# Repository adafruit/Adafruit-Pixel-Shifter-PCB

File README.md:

## Adafruit Pixel Shifter - For Addressable LEDs PCB

<a href="http://www.adafruit.com/products/6066"><br/>
Click here to purchase one from the Adafruit shop</a>

PCB files for the Adafruit Pixel Shifter - For Addressable LEDs. 

Format is EagleCAD schematic and board layout
* https://www.adafruit.com/product/6066

### Description

We've been stocking WS2811-n-friends for a long time, enough to see many iterations and versions of the "one-wire-control" addressable LED pixel. We call them NeoPixels, since the part number itself can change quite a bit, but all have the same idea: send color data to lights and they'll change on their own without having to constantly PWM three or four diodes. Despite this simplicity, we've seen folks struggle with them because of voltage level expectations: some NeoPixel-compatible pixels are very picky and want 5V logic level. Without the right voltage, you get flickering or weird behavior. There's also some funky variants like the TM1814 that want inverted signal levels.

To make wiring easy, so you don't need a separate chip or breadboard, we made this Adafruit Pixel Shifter which can be easily wired in-line to your LED strips or grids or any other shape configuration they come in. On-board is a tiny 5V voltage generator, two shifters and one inverter. Provide it 3-5V power (it only needs a few milliamps) and it will shift up to two signal lines, with one of them also available as an inverted output. All pins are available on 0.1" terminal blocks, use a small flathead screw to attach your solid or stranded core wire, 18AWG to 26AWG.

It's a simple, low-cost, and solder-free way to make your finicky LED setups work with 3.3V logic chips like the RP2040, ESP32 / ESP8266, STM32, SAMD, Raspberry Pi or other modern 3.3V-logic devices. You can also use it for other 5V-logic-needing IC's that require one or two inputs. The onboard 74HCT2G34 shifter can easily handle 10MHz signals, most LED strips use a signal frequency of about 800KHz. A perfect companion to WLED!

You can also use this board as a quick signal debugger: there's a single tiny NeoPixel on the Data line, so you can verify that you're getting valid signal on that pin. If you aren't using NeoPixel protocol, or want to keep it dark, disable it by cutting the trace on the back.

### License

Adafruit invests time and resources providing this open source design, please support Adafruit and open-source hardware by purchasing products from [Adafruit](https://www.adafruit.com)!

Designed by Limor Fried/Ladyada for Adafruit Industries.

Creative Commons Attribution/Share-Alike, all text above must be included in any redistribution. 
See license.txt for additional details.

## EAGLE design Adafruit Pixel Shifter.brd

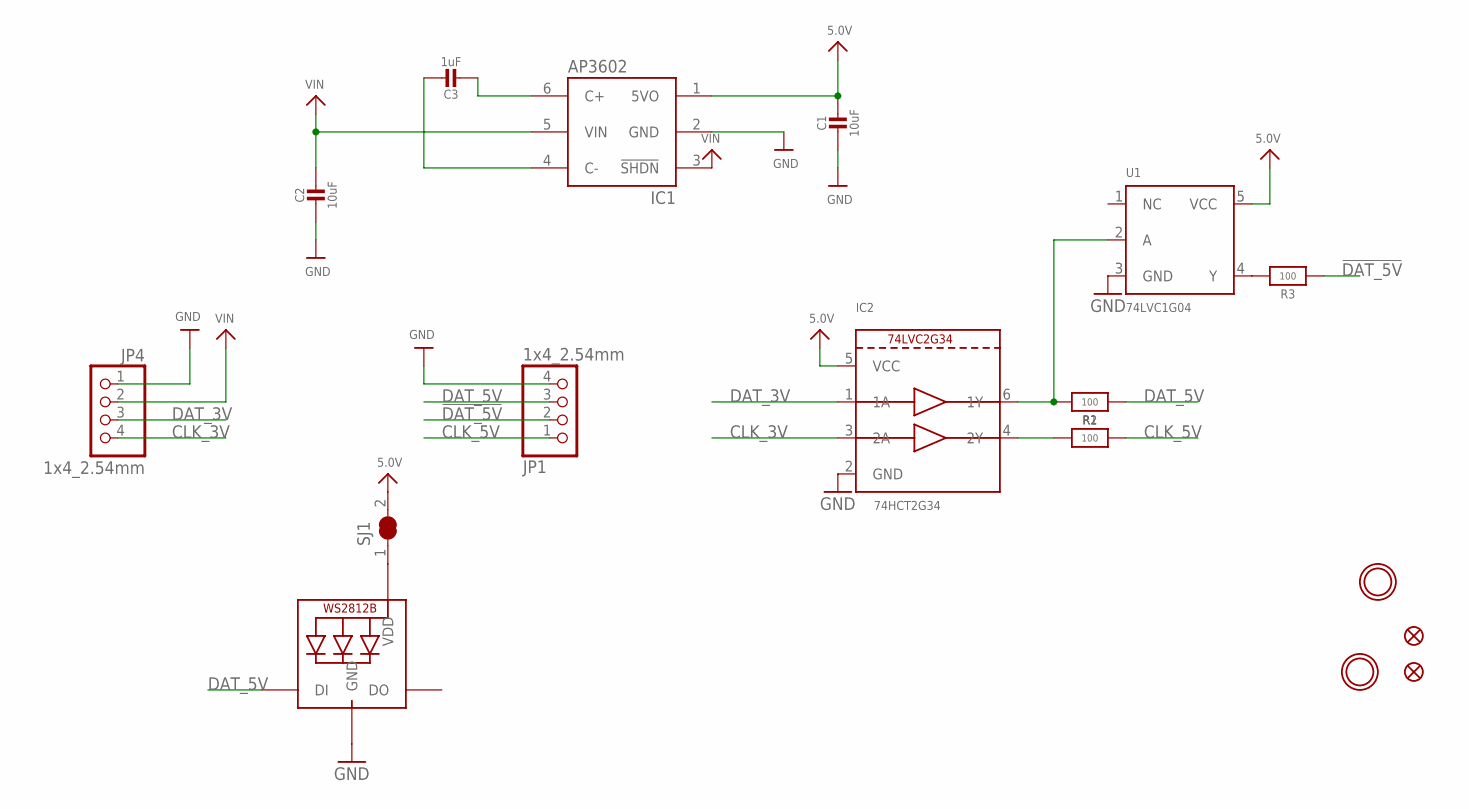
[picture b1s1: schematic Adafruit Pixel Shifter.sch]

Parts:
C1, C2: 10uF; 0805-NO
C3: 1uF; 0603-NO_WIDE
FID1, FID2: FIDUCIAL_0.5MM
IC1: AP3602; SOT23-6
IC2: 74HCT2G34; SC70-6L
JP1, JP4: 1x4_2.54mm; 1X04_2.54MMTERMINAL
LED1: WS2812B_SK6805_1515; SK6805_1515
R1, R2, R3: 100; _0402NO
SJ1: SOLDERJUMPER_CLOSED; SOLDERJUMPER_CLOSEDWIRE
U1: 74LVC1G04; SC70-5
U$6, U$9: MOUNTINGHOLE2.5; MOUNTINGHOLE_2.5_PLATED

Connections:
5.0V: C1.1, IC1.1 (5VO), IC2.5 (VCC), SJ1.2, U1.5 (VCC)
!DAT_5V: JP1.2, R3.2
CLK_3V: IC2.3 (2A), JP4.4
CLK_5V: JP1.1, R1.2
DAT_3V: IC2.1 (1A), JP4.3
DAT_5V: JP1.3, LED1.1 (DI), R2.2
GND: C1.2, C2.2, IC1.2 (GND), IC2.2 (GND), JP1.4, JP4.1, LED1.4 (GND), U1.3 (GND)
unnamed: C3.2, IC1.6 (C+)
unnamed: C3.1, IC1.4 (C-)
unnamed: IC2.4 (2Y), R1.1
unnamed: R3.1, U1.4 (Y)
unnamed: IC2.6 (1Y), R2.1, U1.2 (A)
unnamed: LED1.2 (VDD), SJ1.1
VIN: C2.1, IC1.3 (!SHDN), IC1.5 (VIN), JP4.2

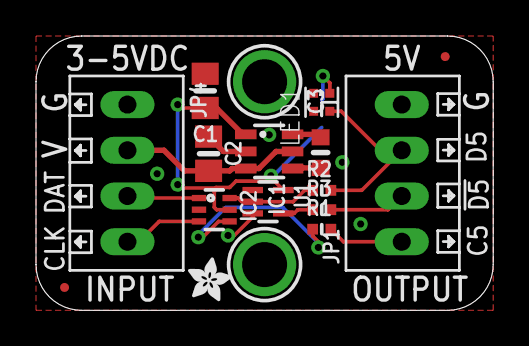
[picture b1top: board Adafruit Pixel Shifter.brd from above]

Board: 2 copper layers, 25.4 x 15.2 mm, 18 parts (1 on the bottom side), 14 nets.

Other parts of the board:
U$11: ADAFRUIT_2.5MM

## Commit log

2024-11-05 cookiecutter

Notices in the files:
parts and their libraries:
microbuilder: This work is placed in the public domain, and may be freely used for commercial and non-commercial work with the following conditions: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
